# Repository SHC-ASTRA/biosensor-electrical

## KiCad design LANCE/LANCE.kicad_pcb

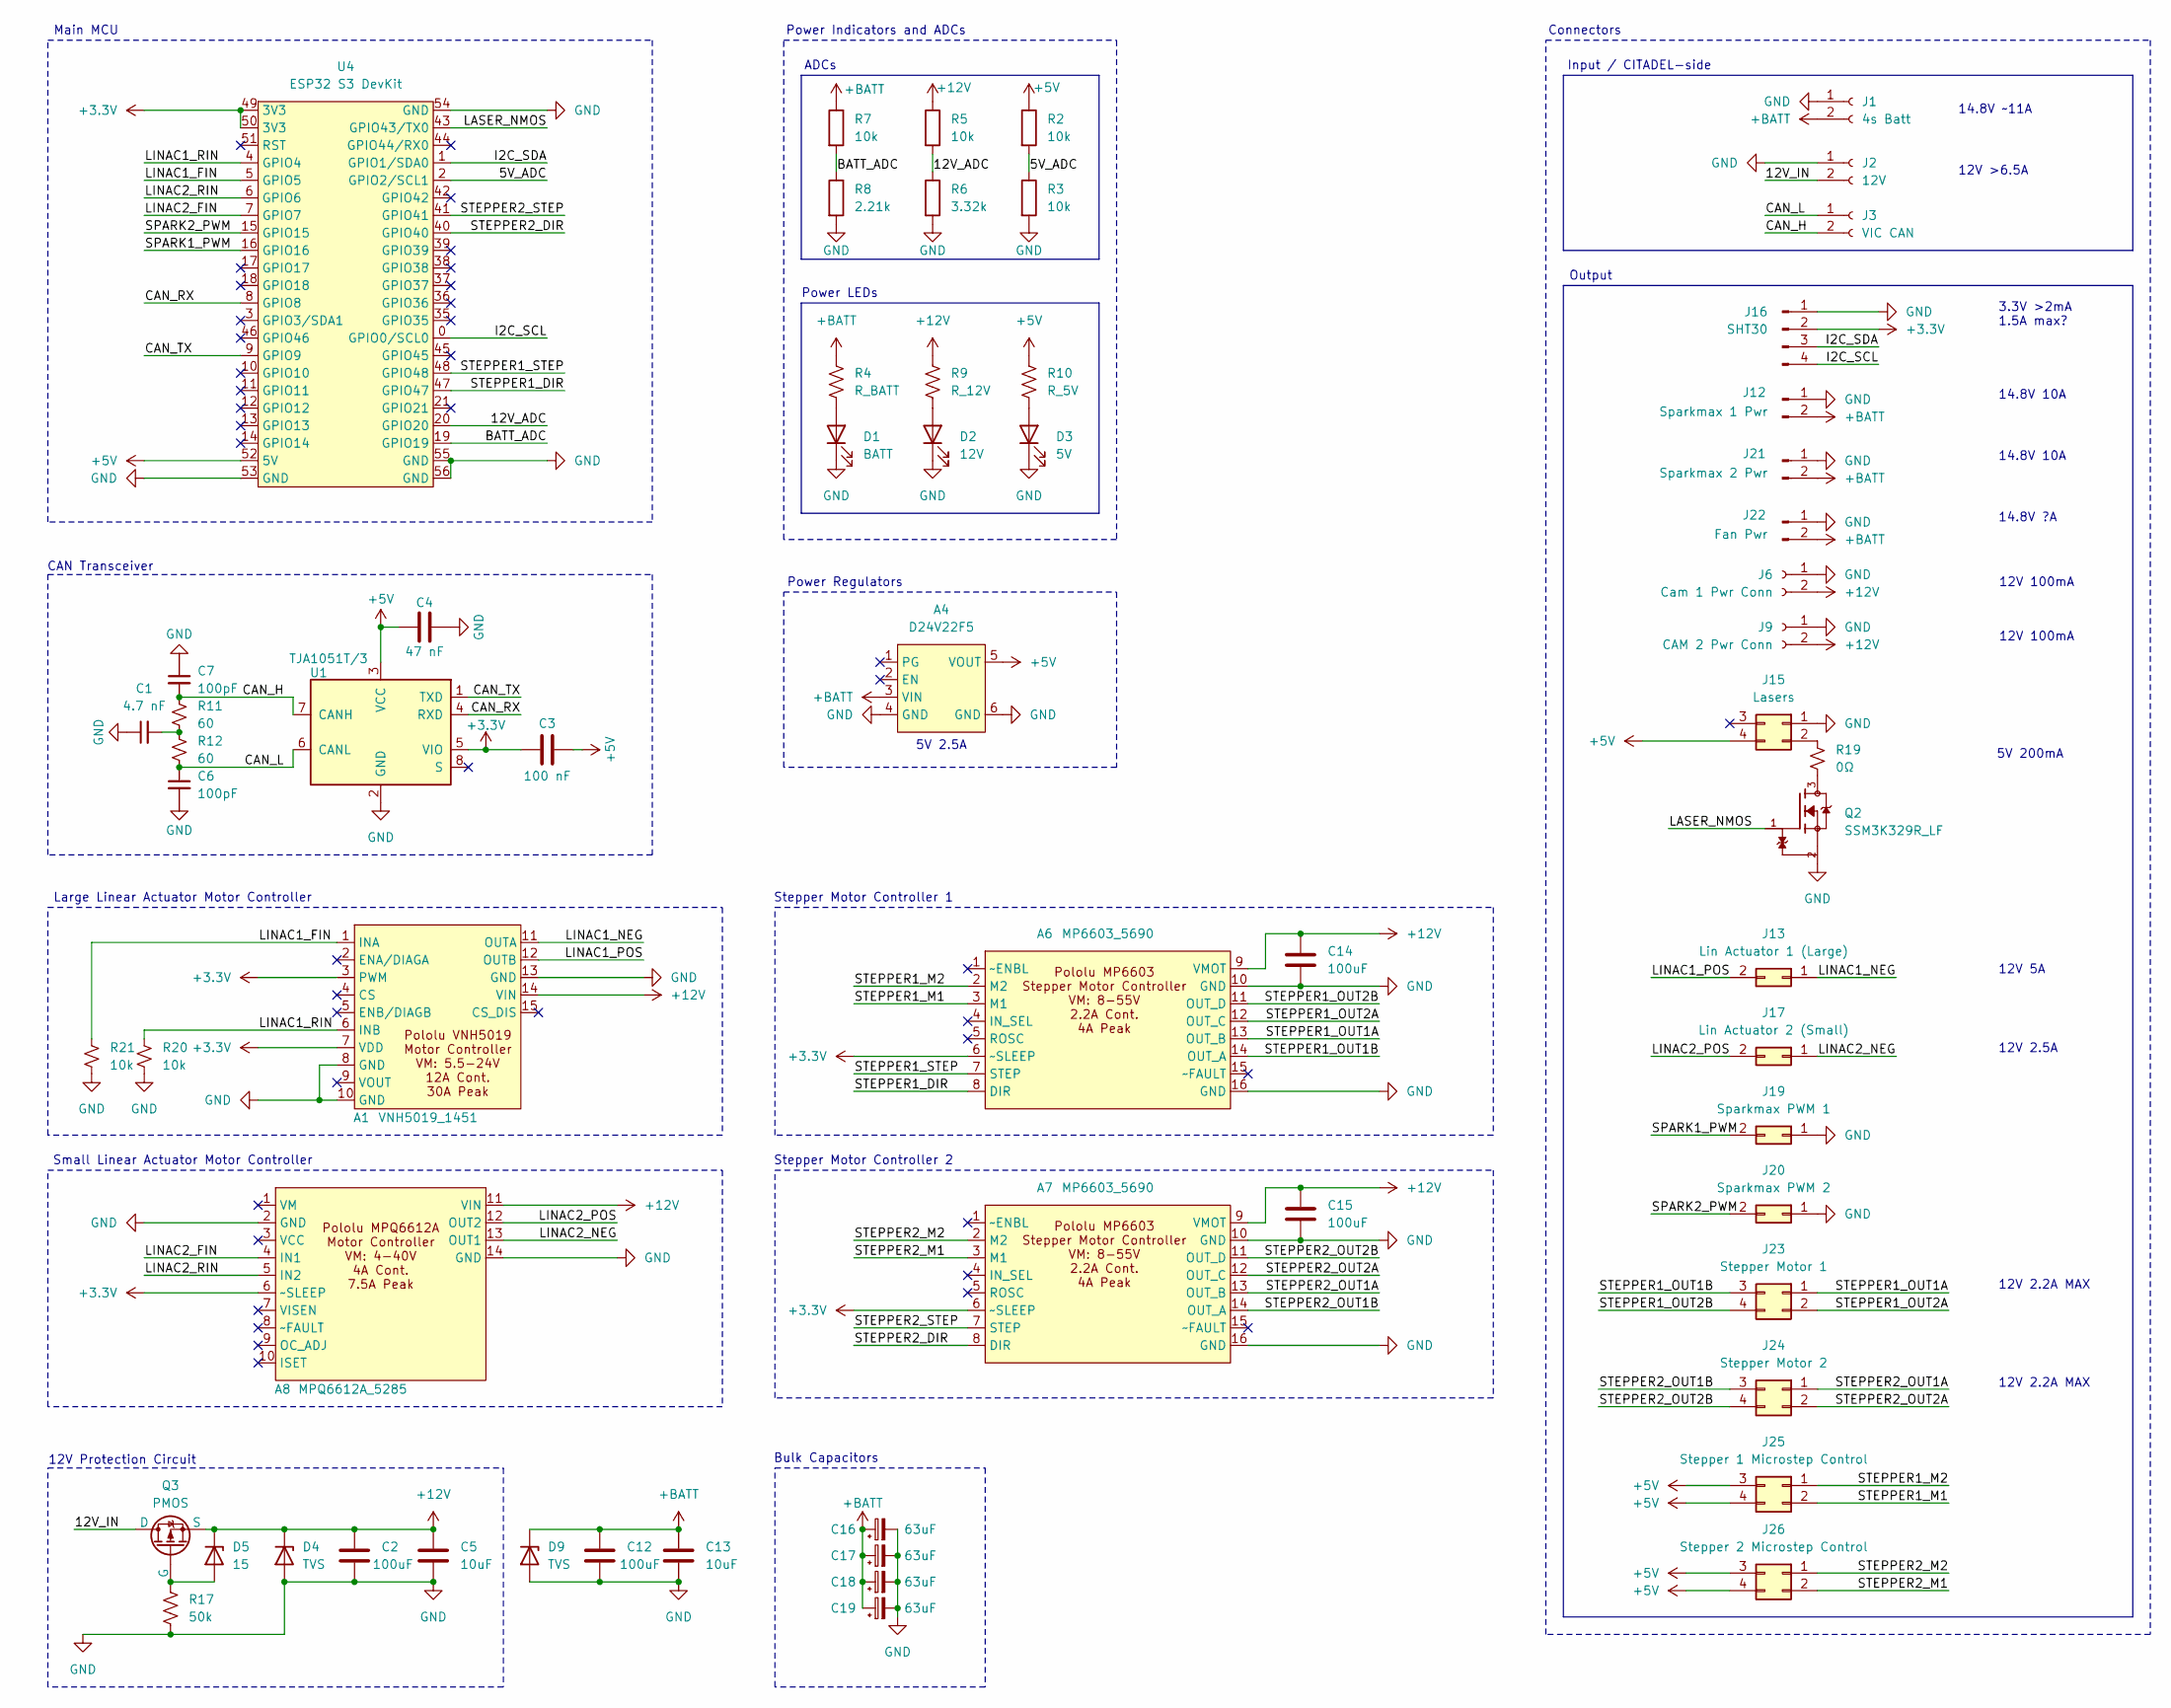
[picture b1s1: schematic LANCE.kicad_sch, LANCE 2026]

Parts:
A1: VNH5019_1451
A4: D24V22F5; D24V22Fx
A6, A7: MP6603_5690; MP6603-5690
A8: MPQ6612A_5285
C1: 4.7 nF; C_0603_1608Metric_Pad1.08x0.95mm_HandSolder
C2, C12, C14, C15: 100uF; C_1210_3225Metric_Pad1.33x2.70mm_HandSolder
C3: 100 nF; C_0603_1608Metric_Pad1.08x0.95mm_HandSolder
C4: 47 nF; C_0603_1608Metric_Pad1.08x0.95mm_HandSolder
C5, C13: 10uF; C_0603_1608Metric_Pad1.08x0.95mm_HandSolder
C6, C7: 100pF; C_0603_1608Metric_Pad1.08x0.95mm_HandSolder
C16, C17, C18, C19: 63uF; CP_Elec_6.3x7.7
D1: BATT; LED_0603_1608Metric_Pad1.05x0.95mm_HandSolder
D2: 12V; LED_0603_1608Metric_Pad1.05x0.95mm_HandSolder
D3: 5V; LED_0603_1608Metric_Pad1.05x0.95mm_HandSolder
D4, D9: TVS; SOD-323HEUS2H_TOS
D5: 15; D_SOD-123
J1: 4s Batt; AMASS_XT60PW-M_1x02_P7.20mm_Horizontal
J2: 12V; AMASS_XT30PW-M_1x02_P2.50mm_Horizontal
J3: VIC CAN; AMASS_XT30PW-F_1x02_P2.50mm_Horizontal
J6: Cam 1 Pwr Conn; AMASS_XT30U-F_1x02_P5.0mm_Vertical
J9: CAM 2 Pwr Conn; AMASS_XT30U-F_1x02_P5.0mm_Vertical
J12: Sparkmax 1 Pwr; AMASS_XT60PW-F_1x02_P7.20mm_Horizontal
J13: Lin Actuator 1 (Large); AMASS_XT30U-F_1x02_P5.0mm_Vertical
J15: Lasers; Molex_Mini-Fit_Jr_5566-04A_2x02_P4.20mm_Vertical
J16: SHT30; Molex_Mini-Fit_Jr_5566-04A_2x02_P4.20mm_Vertical
J17: Lin Actuator 2 (Small); AMASS_XT30U-F_1x02_P5.0mm_Vertical
J19: Sparkmax PWM 1; Molex_Mini-Fit_Jr_5566-02A_2x01_P4.20mm_Vertical
J20: Sparkmax PWM 2; Molex_Mini-Fit_Jr_5566-02A_2x01_P4.20mm_Vertical
J21: Sparkmax 2 Pwr; AMASS_XT60PW-F_1x02_P7.20mm_Horizontal
J22: Fan Pwr; AMASS_XT60PW-F_1x02_P7.20mm_Horizontal
J23: Stepper Motor 1; Molex_Mini-Fit_Jr_5566-04A_2x02_P4.20mm_Vertical
J24: Stepper Motor 2; Molex_Mini-Fit_Jr_5566-04A_2x02_P4.20mm_Vertical
J25: Stepper 1 Microstep Control; PinHeader_2x02_P2.54mm_Vertical
J26: Stepper 2 Microstep Control; PinHeader_2x02_P2.54mm_Vertical
Q2: SSM3K329R_LF; SOT-23F_TOS; PARTREV 1.0
Q3: PMOS; TO-252-2
R2, R3, R5, R7, R20, R21: 10k; R_0603_1608Metric_Pad0.98x0.95mm_HandSolder
R4: R_BATT; R_0603_1608Metric_Pad0.98x0.95mm_HandSolder
R6: 3.32k; R_0603_1608Metric_Pad0.98x0.95mm_HandSolder
R8: 2.21k; R_0603_1608Metric_Pad0.98x0.95mm_HandSolder
R9: R_12V; R_0603_1608Metric_Pad0.98x0.95mm_HandSolder
R10: R_5V; R_0603_1608Metric_Pad0.98x0.95mm_HandSolder
R11, R12: 60; R_0603_1608Metric_Pad0.98x0.95mm_HandSolder
R17: 50k; R_0603_1608Metric_Pad0.98x0.95mm_HandSolder
R19: 0Ω; R_0603_1608Metric_Pad0.98x0.95mm_HandSolder
U1: TJA1051T/3; SOIC-8_3.9x4.9mm_P1.27mm
U4: ESP32 S3 DevKit; ESP32-S3-DevKit_No_Keep-Out_Zone

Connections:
+3.3V: A1.3 (PWM), A1.7 (VDD), A6.6 (~SLEEP), A7.6 (~SLEEP), A8.6 (~SLEEP), C3.2, J16.2, U1.5 (VIO), U4.49 (3V3), U4.50 (3V3)
+5V: A4.5 (VOUT), C3.1, C4.1, J15.4, J25.3, J25.4, J26.3, J26.4, R2.1, R10.1, U1.3 (VCC), U4.52 (5V)
+12V: A1.14 (VIN), A6.9 (VMOT), A7.9 (VMOT), A8.11 (VIN), C2.1, C5.1, C14.1, C15.1, D4.1 (K), D5.1 (K), J6.2, J9.2, Q3.3 (S), R5.1, R9.1
+BATT: A4.3 (VIN), C12.1, C13.1, C16.1, C17.1, C18.1, C19.1, D9.1 (K), J1.2, J12.2, J21.2, J22.2, R4.1, R7.1
/5V_ADC: R2.2, R3.1, U4.2 (GPIO2/SCL1)
/12V_ADC: R5.2, R6.1, U4.20 (GPIO20)
/12V_IN: J2.2, Q3.1 (D)
/BATT_ADC: R7.2, R8.1, U4.19 (GPIO19)
/CAN_H: C7.2, J3.2, R11.1, U1.7 (CANH)
/CAN_L: C6.1, J3.1, R12.2, U1.6 (CANL)
/CAN_RX: U1.4 (RXD), U4.8 (GPIO8)
/CAN_TX: U1.1 (TXD), U4.9 (GPIO9)
/I2C_SCL: J16.4, U4.0 (GPIO0/SCL0)
/I2C_SDA: J16.3, U4.1 (GPIO1/SDA0)
/LASER_NMOS: Q2.1, U4.43 (GPIO43/TX0)
/LINAC1_FIN: A1.1 (INA), R21.2, U4.5 (GPIO5)
/LINAC1_NEG: A1.11 (OUTA), J13.1
/LINAC1_POS: A1.12 (OUTB), J13.2
/LINAC1_RIN: A1.6 (INB), R20.2, U4.4 (GPIO4)
/LINAC2_FIN: A8.4 (IN1), U4.7 (GPIO7)
/LINAC2_NEG: A8.13 (OUT1), J17.1
/LINAC2_POS: A8.12 (OUT2), J17.2
/LINAC2_RIN: A8.5 (IN2), U4.6 (GPIO6)
/SPARK1_PWM: J19.2, U4.16 (GPIO16)
/SPARK2_PWM: J20.2, U4.15 (GPIO15)
/STEPPER1_DIR: A6.8 (DIR), U4.47 (GPIO47)
/STEPPER1_M1: A6.3 (M1), J25.2
/STEPPER1_M2: A6.2 (M2), J25.1
/STEPPER1_OUT1A: A6.13 (OUT_B), J23.1
/STEPPER1_OUT1B: A6.14 (OUT_A), J23.3
/STEPPER1_OUT2A: A6.12 (OUT_C), J23.2
/STEPPER1_OUT2B: A6.11 (OUT_D), J23.4
/STEPPER1_STEP: A6.7 (STEP), U4.48 (GPIO48)
/STEPPER2_DIR: A7.8 (DIR), U4.40 (GPIO40)
/STEPPER2_M1: A7.3 (M1), J26.2
/STEPPER2_M2: A7.2 (M2), J26.1
/STEPPER2_OUT1A: A7.13 (OUT_B), J24.1
/STEPPER2_OUT1B: A7.14 (OUT_A), J24.3
/STEPPER2_OUT2A: A7.12 (OUT_C), J24.2
/STEPPER2_OUT2B: A7.11 (OUT_D), J24.4
/STEPPER2_STEP: A7.7 (STEP), U4.41 (GPIO41)
GND: A1.8 (GND), A1.10 (GND), A1.13 (GND), A4.4 (GND), A4.6 (GND), A6.10 (GND), A6.16 (GND), A7.10 (GND), A7.16 (GND), A8.2 (GND), A8.14 (GND), C1.1, C2.2, C4.2, C5.2, C6.2, C7.1, C12.2, C13.2, C14.2, C15.2, C16.2, C17.2, C18.2, C19.2, D1.1 (K), D2.1 (K), D3.1 (K), D4.2 (A), D9.2 (A), J1.1, J2.1, J6.1, J9.1, J12.1, J15.1, J16.1, J19.1, J20.1, J21.1, J22.1, Q2.2, R3.2, R6.2, R8.2, R17.2, R20.1, R21.1, U1.2 (GND), U4.53 (GND), U4.54 (GND), U4.55 (GND), U4.56 (GND)
unnamed: C1.2, R11.2, R12.1
unnamed: D1.2 (A), R4.2
unnamed: D2.2 (A), R9.2
unnamed: D3.2 (A), R10.2
unnamed: D5.2 (A), Q3.2 (G), R17.1
unnamed: J15.2, R19.1
unnamed: Q2.3, R19.2

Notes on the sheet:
Input / CITADEL-side
12V 5A
Power Regulators
14.8V 10A
ADCs
12V Protection Circuit
5V 2.5A
3.3V >2mA 1.5A max?
14.8V ~11A
Large Linear Actuator Motor Controller
12V 100mA
CAN Transceiver
Stepper Motor Controller 1
12V >6.5A
Stepper Motor Controller 2
Power LEDs
5V 200mA
Main MCU
14.8V ?A
Small Linear Actuator Motor Controller
12V 2.2A MAX
Power Indicators and ADCs
Output
Bulk Capacitors
Connectors
12V 2.5A

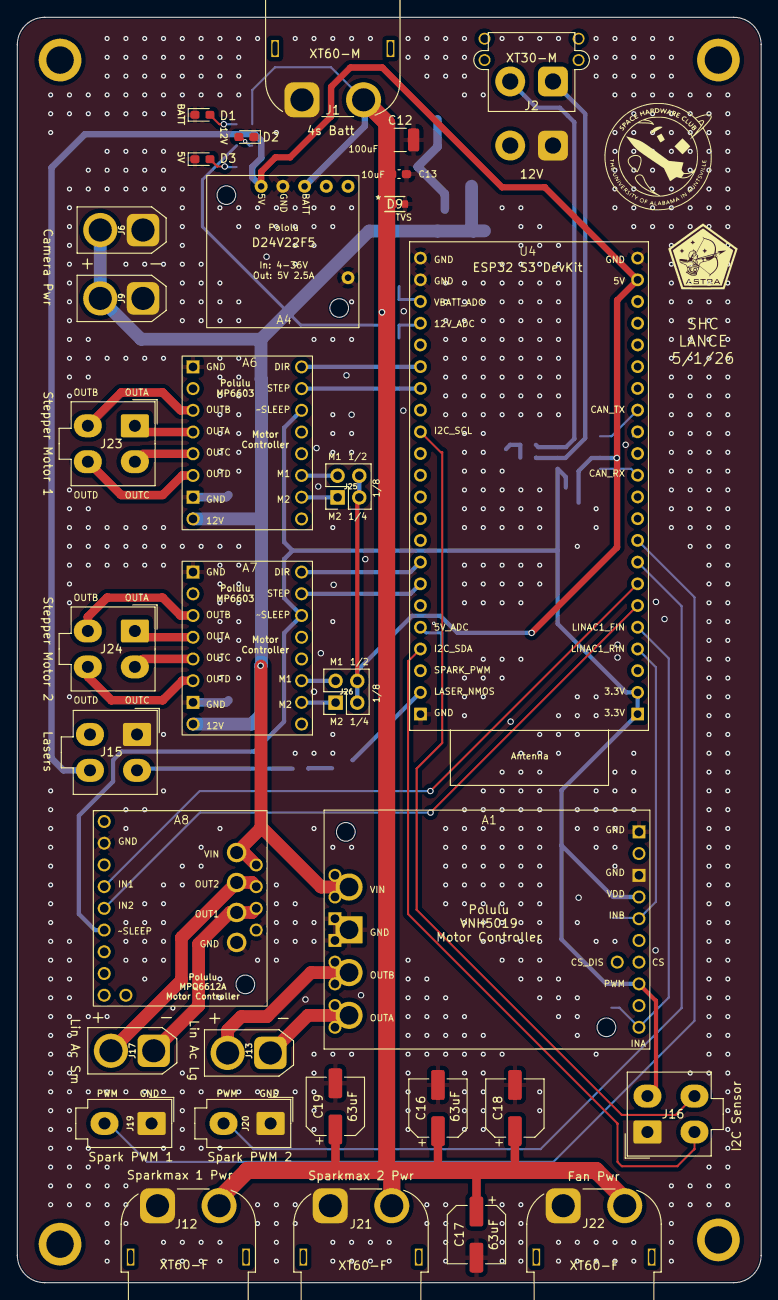
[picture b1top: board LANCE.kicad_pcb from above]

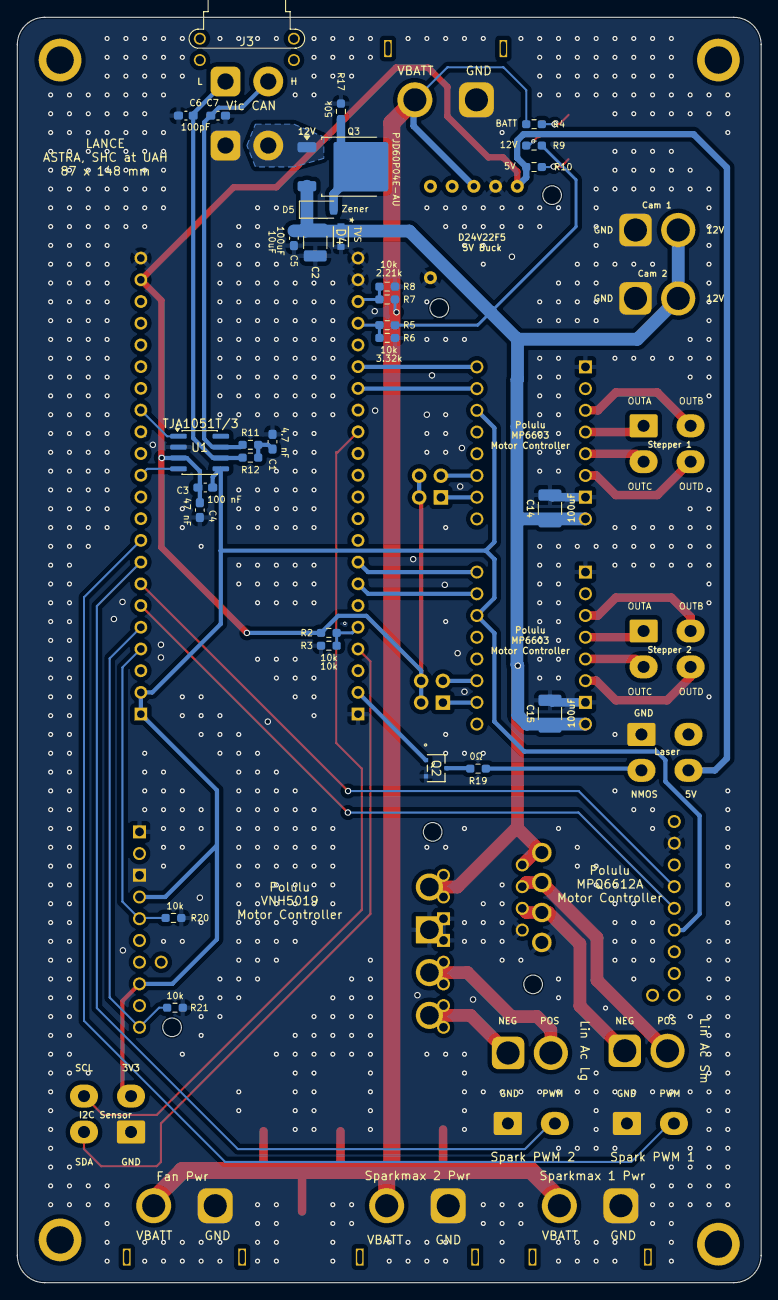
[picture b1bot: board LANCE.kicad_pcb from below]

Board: 2 copper layers, 87.0 x 148.0 mm, 63 parts (30 on the bottom side), 49 nets.

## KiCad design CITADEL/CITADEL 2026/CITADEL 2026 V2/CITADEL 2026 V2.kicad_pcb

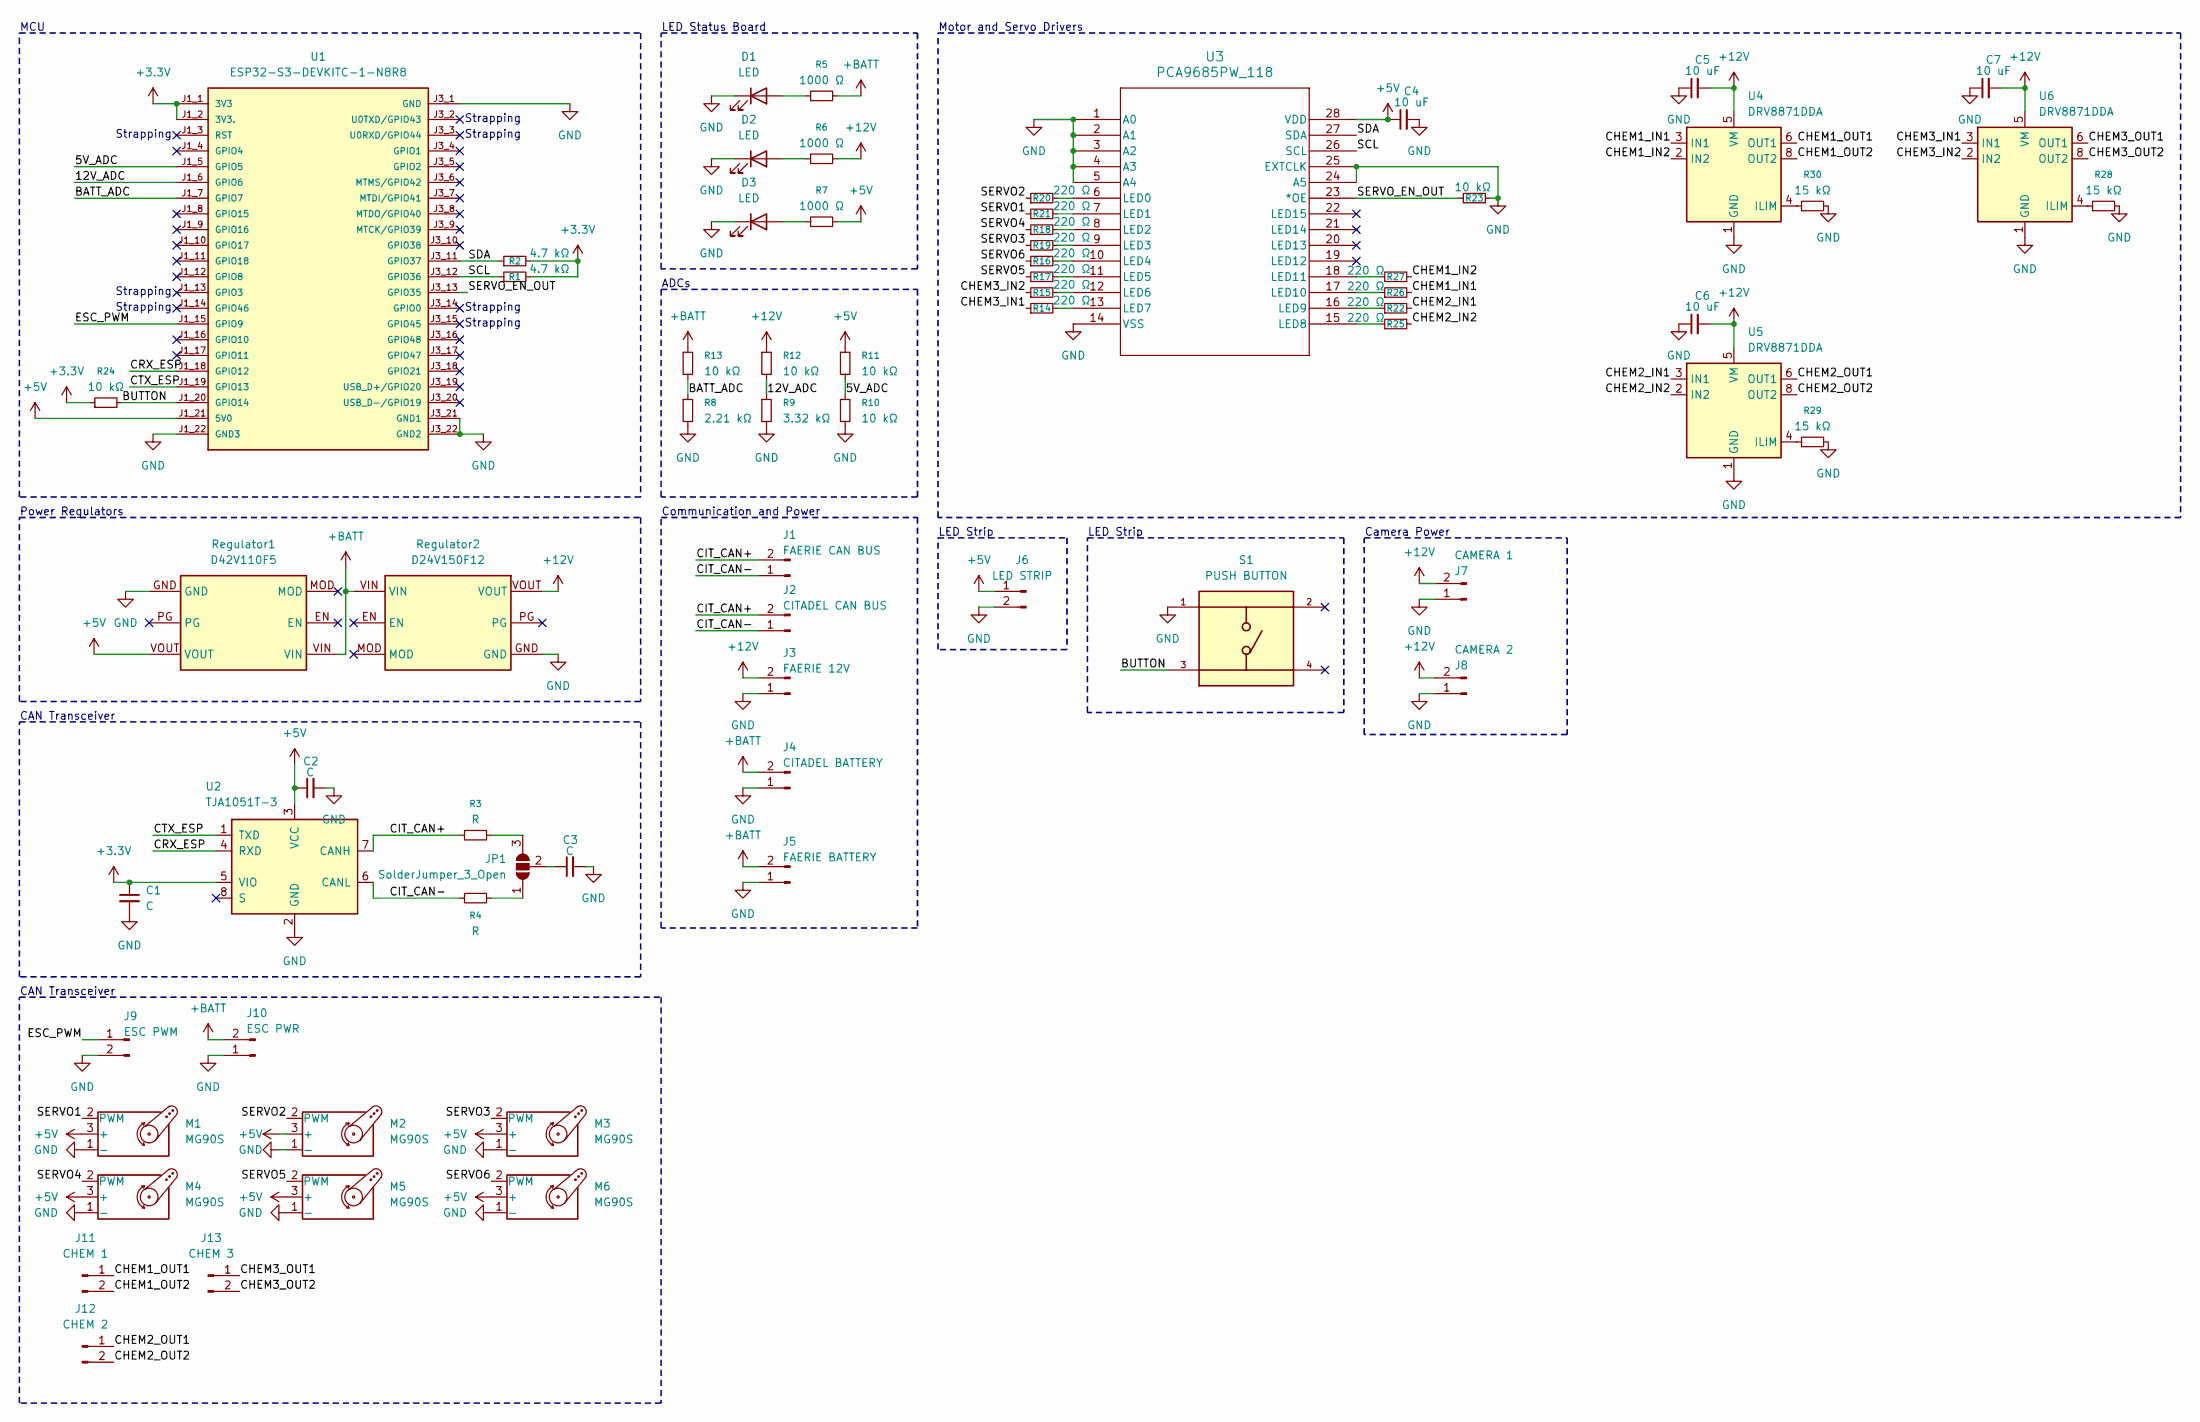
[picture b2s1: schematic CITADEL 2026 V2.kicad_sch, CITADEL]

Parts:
C1, C2, C3: C; C_0603_1608Metric_Pad1.08x0.95mm_HandSolder
C4, C5, C6, C7: 10 uF; C_0603_1608Metric
D1, D2, D3: LED; LED_D3.0mm
J1: FAERIE CAN BUS; AMASS_XT30U-M_1x02_P5.0mm_Vertical
J2: CITADEL CAN BUS; AMASS_XT30U-F_1x02_P5.0mm_Vertical
J3: FAERIE 12V; AMASS_XT30U-F_1x02_P5.0mm_Vertical
J4: CITADEL BATTERY; AMASS_XT60-M_1x02_P7.20mm_Vertical
J5: FAERIE BATTERY; AMASS_XT60-F_1x02_P7.20mm_Vertical
J6: LED STRIP; JST_XH_B2B-XH-A_1x02_P2.50mm_Vertical
J7: CAMERA 1; AMASS_XT30U-F_1x02_P5.0mm_Vertical
J8: CAMERA 2; AMASS_XT30U-F_1x02_P5.0mm_Vertical
J9: ESC PWM; JST_XH_B2B-XH-A_1x02_P2.50mm_Vertical
J10: ESC PWR; AMASS_XT60-F_1x02_P7.20mm_Vertical
J11: CHEM 1; Molex_Mini-Fit_Jr_5566-02A_2x01_P4.20mm_Vertical
J12: CHEM 2; Molex_Mini-Fit_Jr_5566-02A_2x01_P4.20mm_Vertical
J13: CHEM 3; Molex_Mini-Fit_Jr_5566-02A_2x01_P4.20mm_Vertical
JP1: SolderJumper_3_Open; SolderJumper-3_P1.3mm_Open_Pad1.0x1.5mm
M1, M2, M3, M4, M5, M6: MG90S; Molex_Mini-Fit_Jr_5566-04A_2x02_P4.20mm_Vertical
R1, R2: 4.7 kΩ; R_0603_1608Metric
R3, R4: R; R_0603_1608Metric
R5, R6, R7: 1000 Ω; R_0603_1608Metric
R8: 2.21 kΩ; R_0603_1608Metric
R9: 3.32 kΩ; R_0603_1608Metric
R10, R11, R12, R13, R23, R24: 10 kΩ; R_0603_1608Metric
R14, R15, R16, R17, R18, R19, R20, R21, R22, R25, R26, R27: 220 Ω; R_0603_1608Metric
R28, R29, R30: 15 kΩ; R_0603_1608Metric
Regulator1: D42V110F5; D24V15OF5
Regulator2: D24V150F12; D24V15OF5
S1: PUSH BUTTON; SW_TS02-66-60-BK-100-SCR-D; PARTREV 1.0
U1: ESP32-S3-DEVKITC-1-N8R8
U2: TJA1051T-3; SOIC-8_3.9x4.9mm_P1.27mm
U3: PCA9685PW_118; TSSOP28_SOT361-1_NXP
U4, U5, U6: DRV8871DDA; Texas_HTSOP-8-1EP_3.9x4.9mm_P1.27mm_EP2.95x4.9mm_Mask2.4x3.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

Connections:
+3.3V: C1.1, R1.2, R2.2, R24.1, U1.J1_1 (3V3), U1.J1_2 (3V3.), U2.5 (VIO)
+5V: C2.1, C4.1, J6.1, M1.3 (+), M1.4 (+), M2.3 (+), M2.4 (+), M3.3 (+), M3.4 (+), M4.3 (+), M4.4 (+), M5.3 (+), M5.4 (+), M6.3 (+), M6.4 (+), R7.2, R11.1, Regulator1.VOUT, U1.J1_21 (5V0), U2.3 (VCC), U3.28 (VDD)
+12V: C5.2, C6.2, C7.2, J3.2, J7.2, J8.2, R6.2, R12.1, Regulator2.VOUT, U4.5 (VM), U5.5 (VM), U6.5 (VM)
+BATT: J4.2, J5.2, J10.2, R5.2, R13.1, Regulator1.VIN, Regulator2.VIN
/5V_ADC: R10.1, R11.2, U1.J1_5 (GPIO5)
/12V_ADC: R9.1, R12.2, U1.J1_6 (GPIO6)
/BATT_ADC: R8.1, R13.2, U1.J1_7 (GPIO7)
/BUTTON: R24.2, S1.3, U1.J1_20 (GPIO14)
/CHEM1_IN1: R26.2, U4.3 (IN1)
/CHEM1_IN2: R27.2, U4.2 (IN2)
/CHEM1_OUT1: J11.1, U4.6 (OUT1)
/CHEM1_OUT2: J11.2, U4.8 (OUT2)
/CHEM2_IN1: R22.2, U5.3 (IN1)
/CHEM2_IN2: R25.2, U5.2 (IN2)
/CHEM2_OUT1: J12.1, U5.6 (OUT1)
/CHEM2_OUT2: J12.2, U5.8 (OUT2)
/CHEM3_IN1: R14.1, U6.3 (IN1)
/CHEM3_IN2: R15.1, U6.2 (IN2)
/CHEM3_OUT1: J13.1, U6.6 (OUT1)
/CHEM3_OUT2: J13.2, U6.8 (OUT2)
/CIT_CAN+: J1.2, J2.2, R3.2, U2.7 (CANH)
/CIT_CAN-: J1.1, J2.1, R4.2, U2.6 (CANL)
/CRX_ESP: U1.J1_18 (GPIO12), U2.4 (RXD)
/CTX_ESP: U1.J1_19 (GPIO13), U2.1 (TXD)
/ESC_PWM: J9.1, U1.J1_15 (GPIO9)
/SCL: R1.1, U1.J3_12 (GPIO36), U3.26 (SCL)
/SDA: R2.1, U1.J3_11 (GPIO37), U3.27 (SDA)
/SERVO1: M1.2 (PWM), R21.1
/SERVO2: M2.2 (PWM), R20.1
/SERVO3: M3.2 (PWM), R19.1
/SERVO4: M4.2 (PWM), R18.1
/SERVO5: M5.2 (PWM), R17.1
/SERVO6: M6.2 (PWM), R16.1
/SERVO_EN_OUT: R23.2, U1.J3_13 (GPIO35), U3.23 (*OE)
GND: C1.2, C2.2, C3.2, C4.2, C5.1, C6.1, C7.1, D1.1 (K), D2.1 (K), D3.1 (K), J3.1, J4.1, J5.1, J6.2, J7.1, J8.1, J9.2, J10.1, M1.1 (-), M2.1 (-), M3.1 (-), M4.1 (-), M5.1 (-), M6.1 (-), R8.2, R9.2, R10.2, R23.1, R28.2, R29.2, R30.2, Regulator1.GND, Regulator2.GND, S1.1, U1.J1_22 (GND3), U1.J3_1 (GND), U1.J3_21 (GND1), U1.J3_22 (GND2), U2.2 (GND), U3.1 (A0), U3.2 (A1), U3.3 (A2), U3.4 (A3), U3.5 (A4), U3.14 (VSS), U3.24 (A5), U3.25 (EXTCLK), U4.1 (GND), U4.7 (GND), U4.9 (GND), U5.1 (GND), U5.7 (GND), U5.9 (GND), U6.1 (GND), U6.7 (GND), U6.9 (GND)
unnamed: D1.2 (A), R5.1
unnamed: D2.2 (A), R6.1
unnamed: D3.2 (A), R7.1
unnamed: JP1.1 (A), R4.1
unnamed: JP1.3 (B), R3.1
unnamed: C3.1, JP1.2 (C)
unnamed: R20.2, U3.6 (LED0)
unnamed: R21.2, U3.7 (LED1)
unnamed: R18.2, U3.8 (LED2)
unnamed: R19.2, U3.9 (LED3)
unnamed: R16.2, U3.10 (LED4)
unnamed: R17.2, U3.11 (LED5)
unnamed: R15.2, U3.12 (LED6)
unnamed: R14.2, U3.13 (LED7)
unnamed: R25.1, U3.15 (LED8)
unnamed: R22.1, U3.16 (LED9)
unnamed: R26.1, U3.17 (LED10)
unnamed: R27.1, U3.18 (LED11)
unnamed: R30.1, U4.4 (ILIM)
unnamed: R29.1, U5.4 (ILIM)
unnamed: R28.1, U6.4 (ILIM)

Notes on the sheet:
CAN Transceiver
Motor and Servo Drivers
Strapping
Camera Power
MCU
ADCs
LED Status Board
Power Regulators
Communication and Power
LED Strip

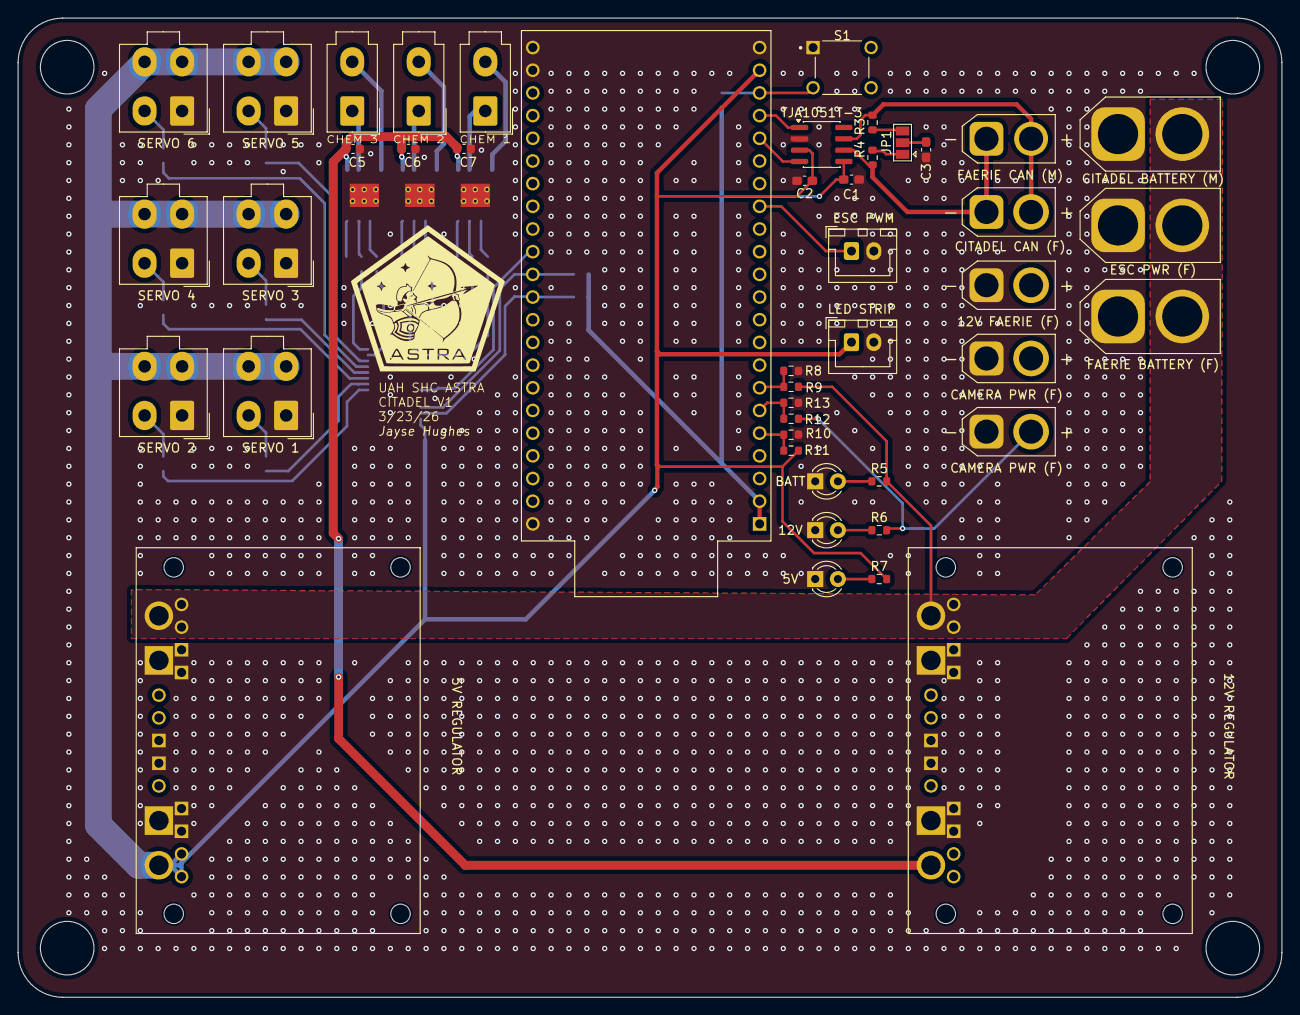
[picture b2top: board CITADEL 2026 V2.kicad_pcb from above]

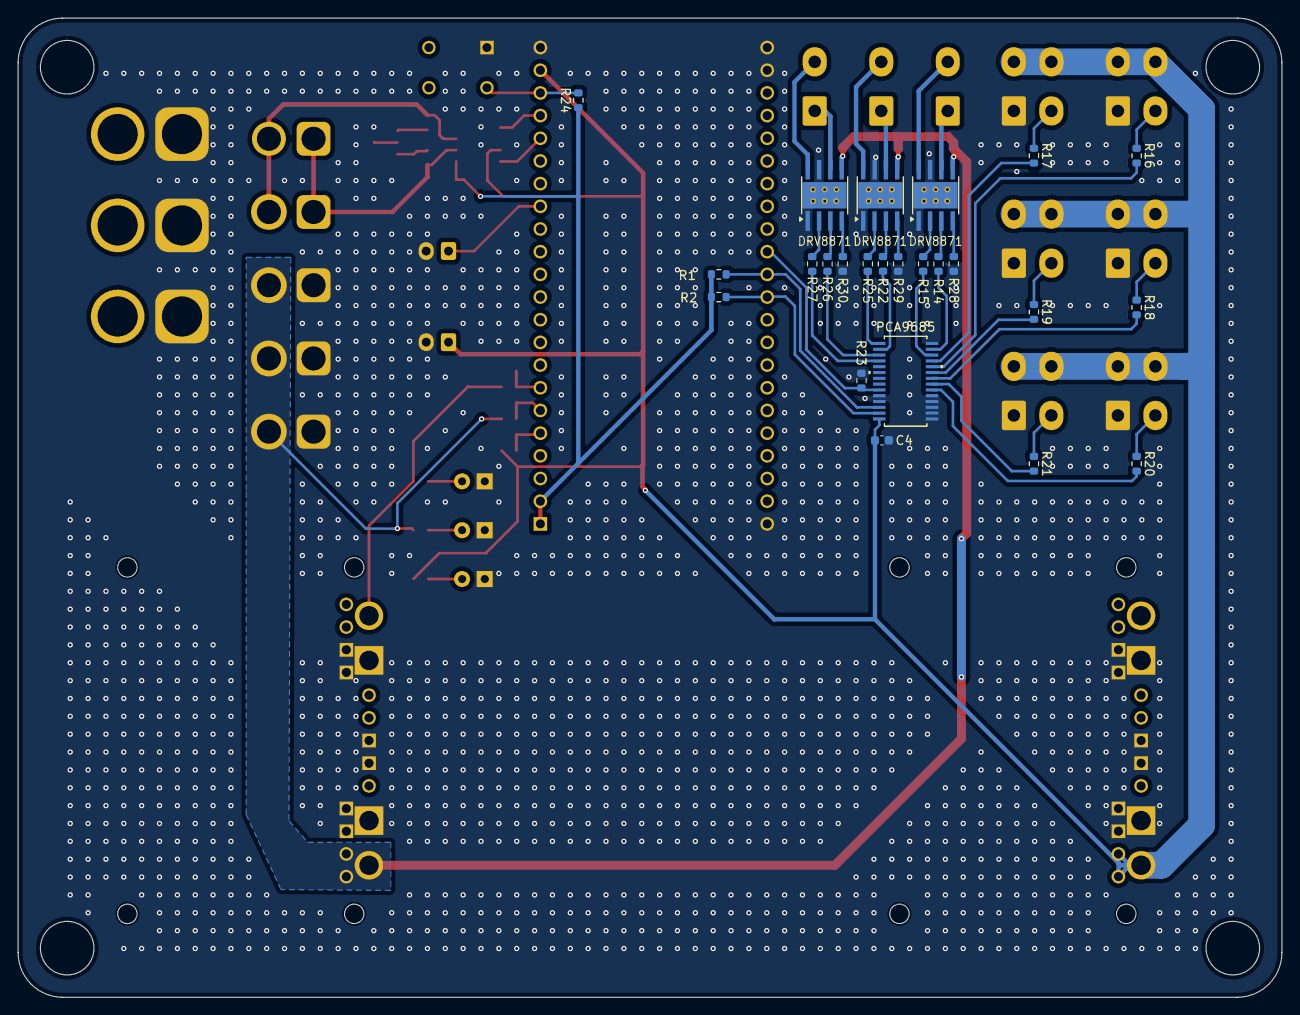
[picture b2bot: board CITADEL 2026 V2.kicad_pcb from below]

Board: 2 copper layers, 141.5 x 109.7 mm, 69 parts (24 on the bottom side), 56 nets.

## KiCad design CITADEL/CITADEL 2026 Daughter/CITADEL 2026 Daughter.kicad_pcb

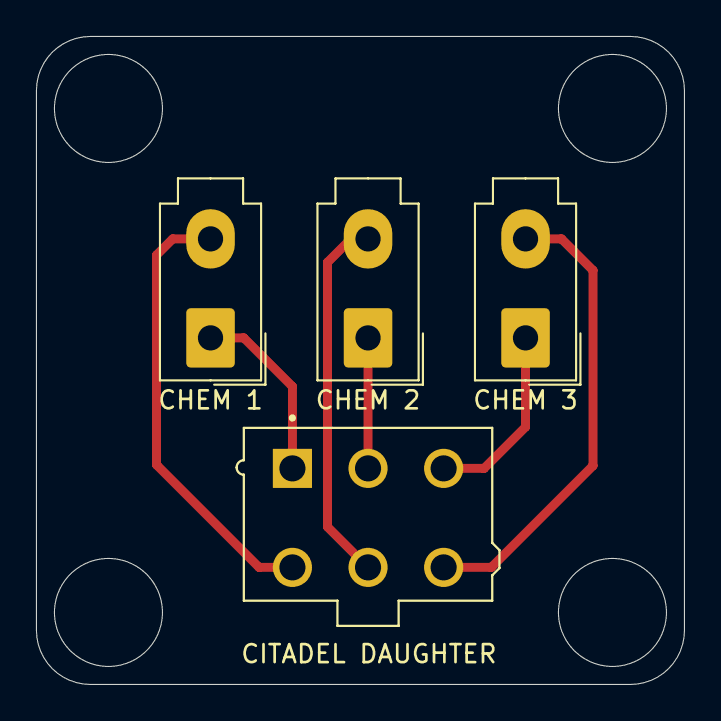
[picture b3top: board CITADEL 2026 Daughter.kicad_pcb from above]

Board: 2 copper layers, 36.0 x 36.0 mm, 4 parts (0 on the bottom side), 6 nets.

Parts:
CHEM 1: CHEM 1; Molex_Mini-Fit_Jr_5566-02A_2x01_P4.20mm_Vertical
CHEM 2: CHEM 2; Molex_Mini-Fit_Jr_5566-02A_2x01_P4.20mm_Vertical
CHEM 3: CHEM 3; Molex_Mini-Fit_Jr_5566-02A_2x01_P4.20mm_Vertical
CITADEL DAUGHTER: CITADEL DAUGHTER; MOLEX_0039281063

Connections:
/CHEM1_OUT1: CHEM 1.1, CITADEL DAUGHTER.1
/CHEM1_OUT2: CHEM 1.2, CITADEL DAUGHTER.4
/CHEM2_OUT1: CHEM 2.1, CITADEL DAUGHTER.2
/CHEM2_OUT2: CHEM 2.2, CITADEL DAUGHTER.5
/CHEM3_OUT1: CHEM 3.1, CITADEL DAUGHTER.3
/CHEM3_OUT2: CHEM 3.2, CITADEL DAUGHTER.6

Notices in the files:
CITADEL/BioSensor.kicad_pcb:
(C)2020 Adrian Studer
CERN Open Hardware Licence Version 2 - Permissive
parts and their libraries:
Copyright 2021 Accelerated Designs. All rights reserved.
